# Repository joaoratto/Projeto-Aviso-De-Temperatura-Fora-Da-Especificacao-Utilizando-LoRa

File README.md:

# Projeto Aviso de Temperatura Fora da Especificação Utilizando LoRa

Dispositivo para identificar variação de temperatura e informar um dispositivo receptor

Em desenvolvimento

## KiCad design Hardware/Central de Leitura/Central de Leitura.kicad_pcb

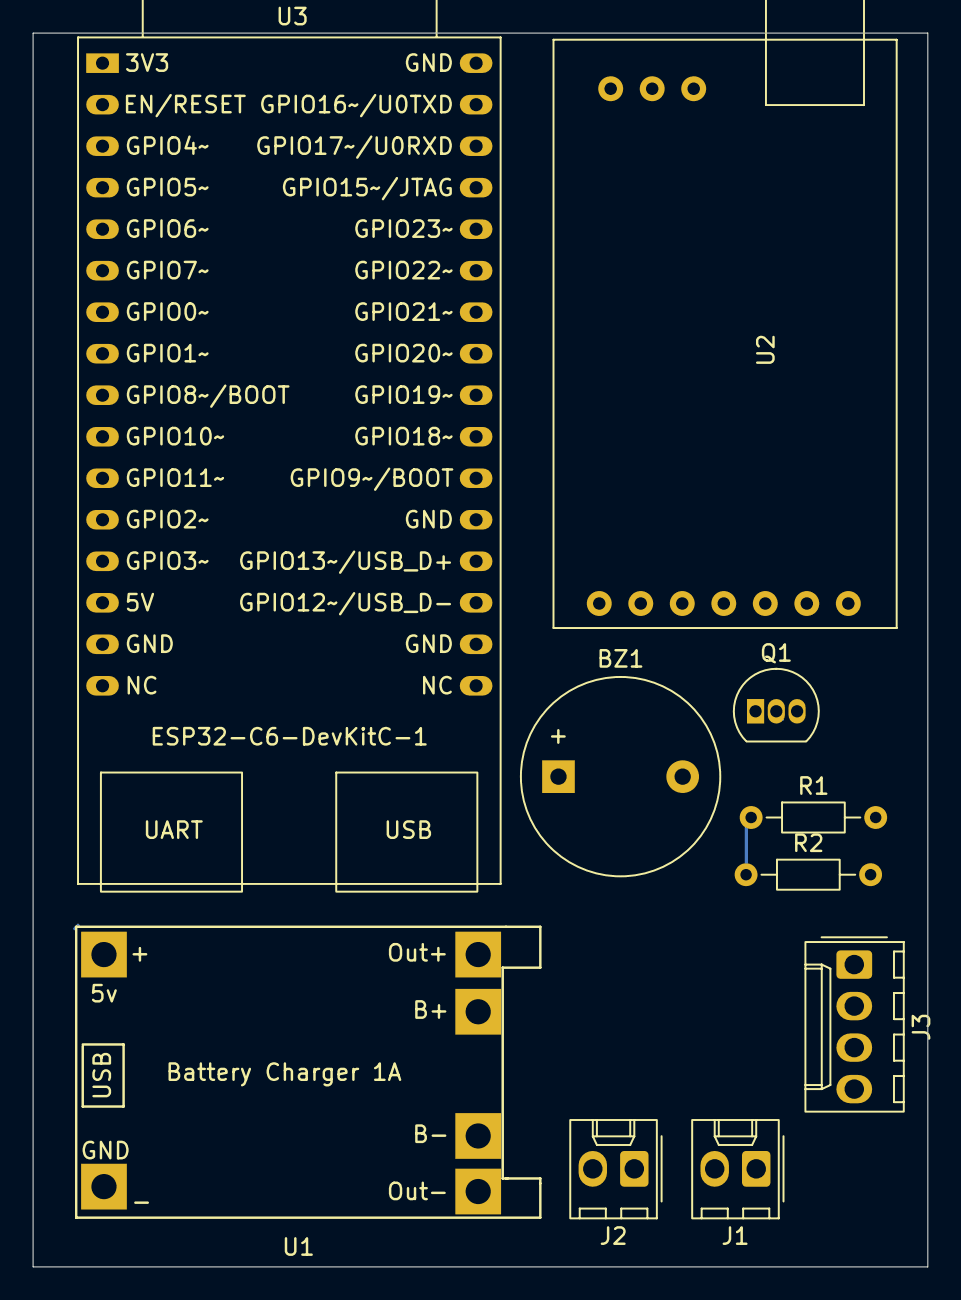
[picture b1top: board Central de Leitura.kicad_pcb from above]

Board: 2 copper layers, 54.8 x 75.5 mm, 10 parts (0 on the bottom side), 8 nets.

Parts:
BZ1: Buzzer; Buzzer_12x9.5RM7.6
J1: Bateria; Molex_KK-254_AE-6410-02A_1x02_P2.54mm_Vertical
J2: Fonte; Molex_KK-254_AE-6410-02A_1x02_P2.54mm_Vertical
J3: Modulo ZMPT101B; Molex_KK-254_AE-6410-04A_1x04_P2.54mm_Vertical
Q1: BC338; TO-92_Inline
R1, R2: 100R; R_Axial_DIN0204_L3.6mm_D1.6mm_P7.62mm_Horizontal
U1: Módulo TP4056; TP4056-18650
U2: E32-433T20D; E32-xxxT20D
U3: ESP32-C6-DevKitC-1

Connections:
+5V: J1.1, J3.1, Q1.1 (C), U1.3 (Out+), U1.5 (B+), U2.6 (VCC), U3.14 (5V)
+5V Fonte: J2.1, U1.1 (5v)
B-: J1.2, U1.6 (B-)
Buzzer: R1.1, R2.1, U3.26 (GPIO21)
GND: BZ1.2 (-), J2.2, J3.3, J3.4, U1.2 (GND), U1.4 (Out-), U2.7 (GND), U3.15 (GND), U3.18 (GND), U3.21 (GND), U3.32 (GND)
unnamed: BZ1.1 (+), Q1.3 (E)
unnamed: J3.2, R2.2
unnamed: Q1.2 (B), R1.2

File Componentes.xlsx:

Itens | Descrição | Quantidade | Link Compra | Link Referência | Compra solicitada? | Valor unitário | Total/Item |  |  | VALOR TOTAL | 1147.4299999999998
E32-433T20D | Módulo LoRa | 3 | https://www.mercadolivre.com.br/modulo-rf-wireless-lora-433m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 | https://www.cdebyte.com/products/E32-433T20D | Sim | 112.95 | 338.85
Antena 433mhz Sma 6dbi | Antena para modulo LoRa | 3 | https://www.mercadolivre.com.br/antena-433mhz-sma-6dbi-19cm/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 |  | Sim | 36 | 108
 | Tomada Steck Fêmea (parede) |  |  |  |  |  | 0
 | Tomada Steck Fêmea (painel) |  |  |  |  |  | 0
 | Tomada Steck Macho |  |  |  |  |  | 0
Buzzer 5V Bip Contínuo - PCI 12mm | Buzzer | 2 | https://www.proesi.com.br/buzzer-5v-bip-continuo-pci-12mm-os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 |  | Sim | 3.65 | 7.3
 | Placa fenolite (verificar o tamanho das placas) |  |  |  |  |  | 0
Fonte 5V 3A | Fonte de alimentação | 2 | https://www.fontesmeanwell.com.br/fonte-chaveada-15w-85-264v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 |  | Sim | 70.45 | 140.9
Bateria 3.7V 10A | Bateria do leitor de tensão | 1 | https://www.jheletronico.com.br/pack-de-baterias-18650-li-io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 |  | Sim | 79.900000000000006 | 79.900000000000006
Bateria 3.7v 2100mah Litio | Bateria do receptor | 1 | https://www.jheletronico.com.br/bateria-li-po-37v-21a-77wh-g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 |  | Sim | 29.9 | 29.9
Kit 10 Módulo Tp4056 Carregador De Bateria Usb Tipo C 5v 1a | Carregador de bateria | 1 | https://www.mercadolivre.com.br/kit-10-modulo-tp4056-carrega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 |  | Sim | 31.87 | 31.87
Módulo Sensor De Tensão 0 a 250V AC - ZMPT101B | Sensor de tensão | 1 | https://www.proesi.com.br/modulo-sensor-de-tens-o-ac-0-a-250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 |  | Sim | 33.92 | 33.92
ESP32-C6-DevKitC-1 | Módulo ESP32 | 3 | https://www.usinainfo.com.br/esp32/esp32-c6-devkitc-1-com-wi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 |  | Sim | 84.31 | 252.93
Kit de Capacitores | Capacitores | 1 | https://www.mercadolivre.com.br/kit-200-capacitor-eletroliti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 |  | Sim | 54.33 | 54.33
MB-102 - Protoboard 830 Pontos | Protoboard | 1 | https://www.proesi.com.br/mb-102-protoboard-830-pontos |  | Sim | 21.58 | 21.58
BC338 - Transistor NPN, 25V/800mA (TO-92) | Transistor BC338 | 10 | https://www.proesi.com.br/bc338-transistor-to92 |  | Sim | 0.33 | 3.3000000000000003
Chave Táctil KFC-A06 - 6X6X5mm - 4T - 180° | push button | 20 | https://www.proesi.com.br/chave-tactil-kfc-a06-6x6x5mm-4t-180 |  | Sim | 0.22 | 4.4000000000000004
Gaveteiro Organizador G 28X17,5X4cm | Caixa organizadora | 1 | https://www.proesi.com.br/gaveteiro-organizador-g-28x17-5x4cm |  | Sim | 40.25 | 40.25
 | Conector KK (definir) |  |  |  |  |  | 0
 | Terminal KK |  |  |  |  |  | 0
 | Barra de pinos macho (definir) |  |  |  |  |  | 0
 | Barra de pinos fêmea (definir) |  |  |  |  |  | 0
